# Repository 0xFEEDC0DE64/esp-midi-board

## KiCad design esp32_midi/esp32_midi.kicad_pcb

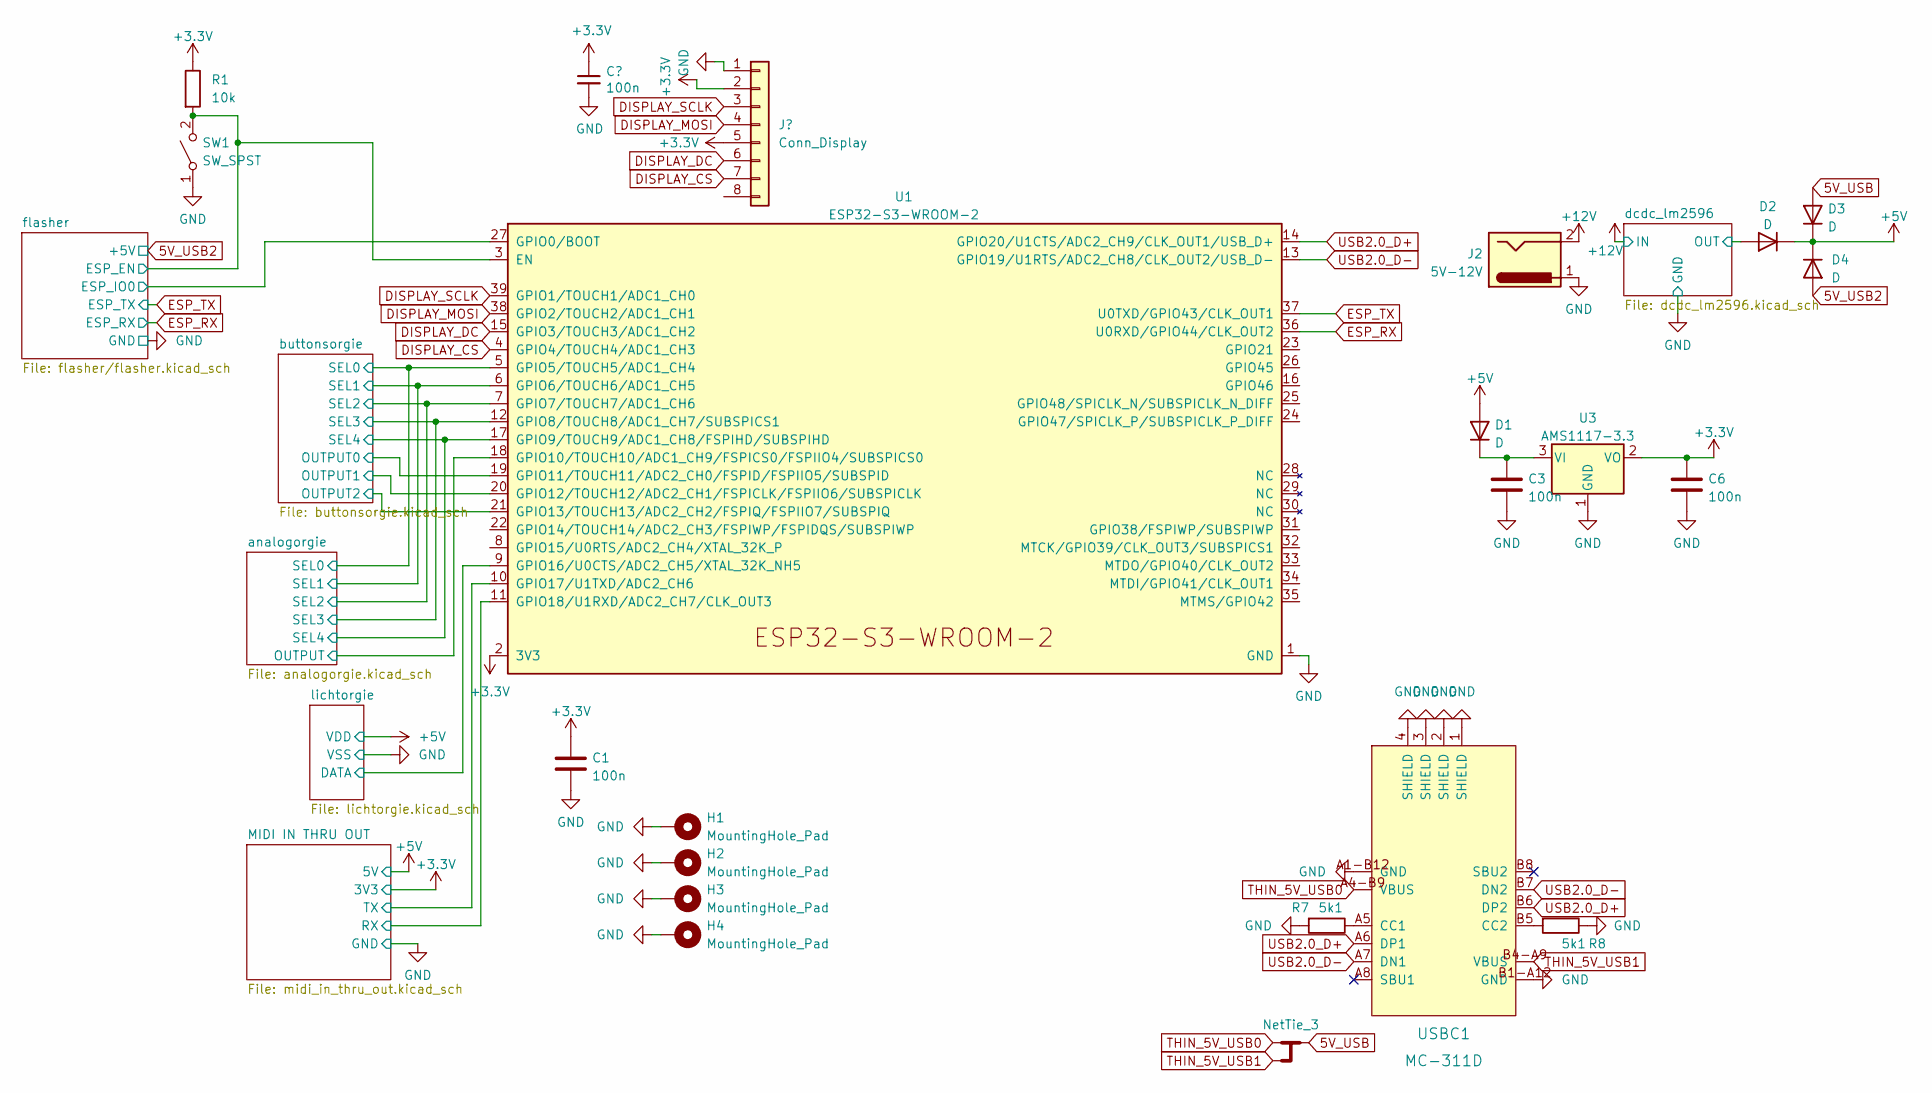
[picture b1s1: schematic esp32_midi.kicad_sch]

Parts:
C1, C3, C6: 100n; C_1206_3216Metric
C2: 100n; C_1206_3216Metric; LCSC Part # C1525
D1, D2, D3, D4: D; D_SOD-123
H1, H2, H3, H4: MountingHole_Pad; MountingHole_4mm_Pad_Via
J1: Conn_Display; PinHeader_1x08_P2.54mm_Vertical
J2: 5V-12V; BarrelJack_Wuerth_6941xx301002
NT102: NetTie_3; NetTie-3_SMD_Pad0.5mm
R1: 10k; R_1206_3216Metric
R7, R8: 5k1; R_1206_3216Metric; LCSC Part # C25905
SW1: SW_SPST; SW_PUSH_6mm_H13mm
U1: ESP32-S3-WROOM-2
U3: AMS1117-3.3; SOT-223-3_TabPin2
USBC1: MC-311D; USB-C-SMD_MC-311D; JLC Part Extended Part

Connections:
5V_USB: D3.2 (A), NT102.2
5V_USB2: D4.2 (A); also elsewhere on the board
+3.3V: C1.1, C2.1, C6.1, J1.2, J1.5, R1.1, U1.2 (3V3), U3.2 (VO); also elsewhere on the board
+5V: D1.2 (A), D2.1 (K), D3.1 (K), D4.1 (K); also elsewhere on the board
+12V: J2.2; also elsewhere on the board
/MIDI IN THRU OUT/RX: U1.11 (GPIO18/U1RXD/ADC2_CH7/CLK_OUT3); also elsewhere on the board
/MIDI IN THRU OUT/TX: U1.10 (GPIO17/U1TXD/ADC2_CH6); also elsewhere on the board
/OUTPUT: U1.18 (GPIO10/TOUCH10/ADC1_CH9/FSPICS0/FSPIIO4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)
/analogorgie/SEL0: U1.5 (GPIO5/TOUCH5/ADC1_CH4); also elsewhere on the board
/analogorgie/SEL1: U1.6 (GPIO6/TOUCH6/ADC1_CH5); also elsewhere on the board
/analogorgie/SEL2: U1.7 (GPIO7/TOUCH7/ADC1_CH6); also elsewhere on the board
/analogorgie/SEL3: U1.12 (GPIO8/TOUCH8/ADC1_CH7/SUBSPICS1); also elsewhere on the board
/analogorgie/SEL4: U1.17 (GPIO9/TOUCH9/ADC1_CH8/FSPIHD/SUBSPIHD); also elsewhere on the board
/buttonsorgie/OUTPUT0: U1.19 (GPIO11/TOUCH11/ADC2_CH0/FSPID/FSPIIO5/S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); also elsewhere on the board
/buttonsorgie/OUTPUT1: U1.20 (GPIO12/TOUCH12/ADC2_CH1/FSPICLK/FSPIIO6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); also elsewhere on the board
/buttonsorgie/OUTPUT2: U1.21 (GPIO13/TOUCH13/ADC2_CH2/FSPIQ/FSPIIO7/S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); also elsewhere on the board
/flasher/ESP_EN: R1.2, SW1.2 (B), U1.3 (EN); also elsewhere on the board
/flasher/ESP_IO0: U1.27 (GPIO0/BOOT); also elsewhere on the board
/lichtorgie/DATA: U1.9 (GPIO16/U0CTS/ADC2_CH5/XTAL_32K_NH5); also elsewhere on the board
DICK1: D2.2 (A); also elsewhere on the board
DISPLAY_CS: J1.7, U1.4 (GPIO4/TOUCH4/ADC1_CH3)
DISPLAY_DC: J1.6, U1.15 (GPIO3/TOUCH3/ADC1_CH2)
DISPLAY_MOSI: J1.4, U1.38 (GPIO2/TOUCH2/ADC1_CH1)
DISPLAY_SCLK: J1.3, U1.39 (GPIO1/TOUCH1/ADC1_CH0)
ESP_RX: U1.36 (U0RXD/GPIO44/CLK_OUT2); also elsewhere on the board
ESP_TX: U1.37 (U0TXD/GPIO43/CLK_OUT1); also elsewhere on the board
GND: C1.2, C2.2, C3.2, C6.2, H1.1, H2.1, H3.1, H4.1, J1.1, J2.1, R7.2, R8.1, SW1.1 (A), U1.1 (GND), U1.40 (GND), U1.41 (GND), U3.1 (GND), USBC1.1 (SHIELD), USBC1.2 (SHIELD), USBC1.3 (SHIELD), USBC1.4 (SHIELD), USBC1.A1-B12 (GND), USBC1.B1-A12 (GND); also elsewhere on the board
unnamed: C3.1, D1.1 (K), U3.3 (VI)
unnamed 400: R7.1; also elsewhere on the board
unnamed 401: R8.2; also elsewhere on the board
THIN_5V_USB0: NT102.1, USBC1.A4-B9 (VBUS); also elsewhere on the board
THIN_5V_USB1: NT102.3, USBC1.B4-A9 (VBUS); also elsewhere on the board
USB2.0_D+: U1.14 (GPIO20/U1CTS/ADC2_CH9/CLK_OUT1/USB_D+), USBC1.A6 (DP1), USBC1.B6 (DP2); also elsewhere on the board
USB2.0_D-: U1.13 (GPIO19/U1RTS/ADC2_CH8/CLK_OUT2/USB_D-), USBC1.A7 (DN1), USBC1.B7 (DN2); also elsewhere on the board

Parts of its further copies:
R51, R52: 5k1; R_1206_3216Metric; LCSC Part # C25905

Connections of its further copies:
GND: R51.2, R52.1; also elsewhere on the board
unnamed 402: R51.1; also elsewhere on the board
unnamed 403: R52.2; also elsewhere on the board

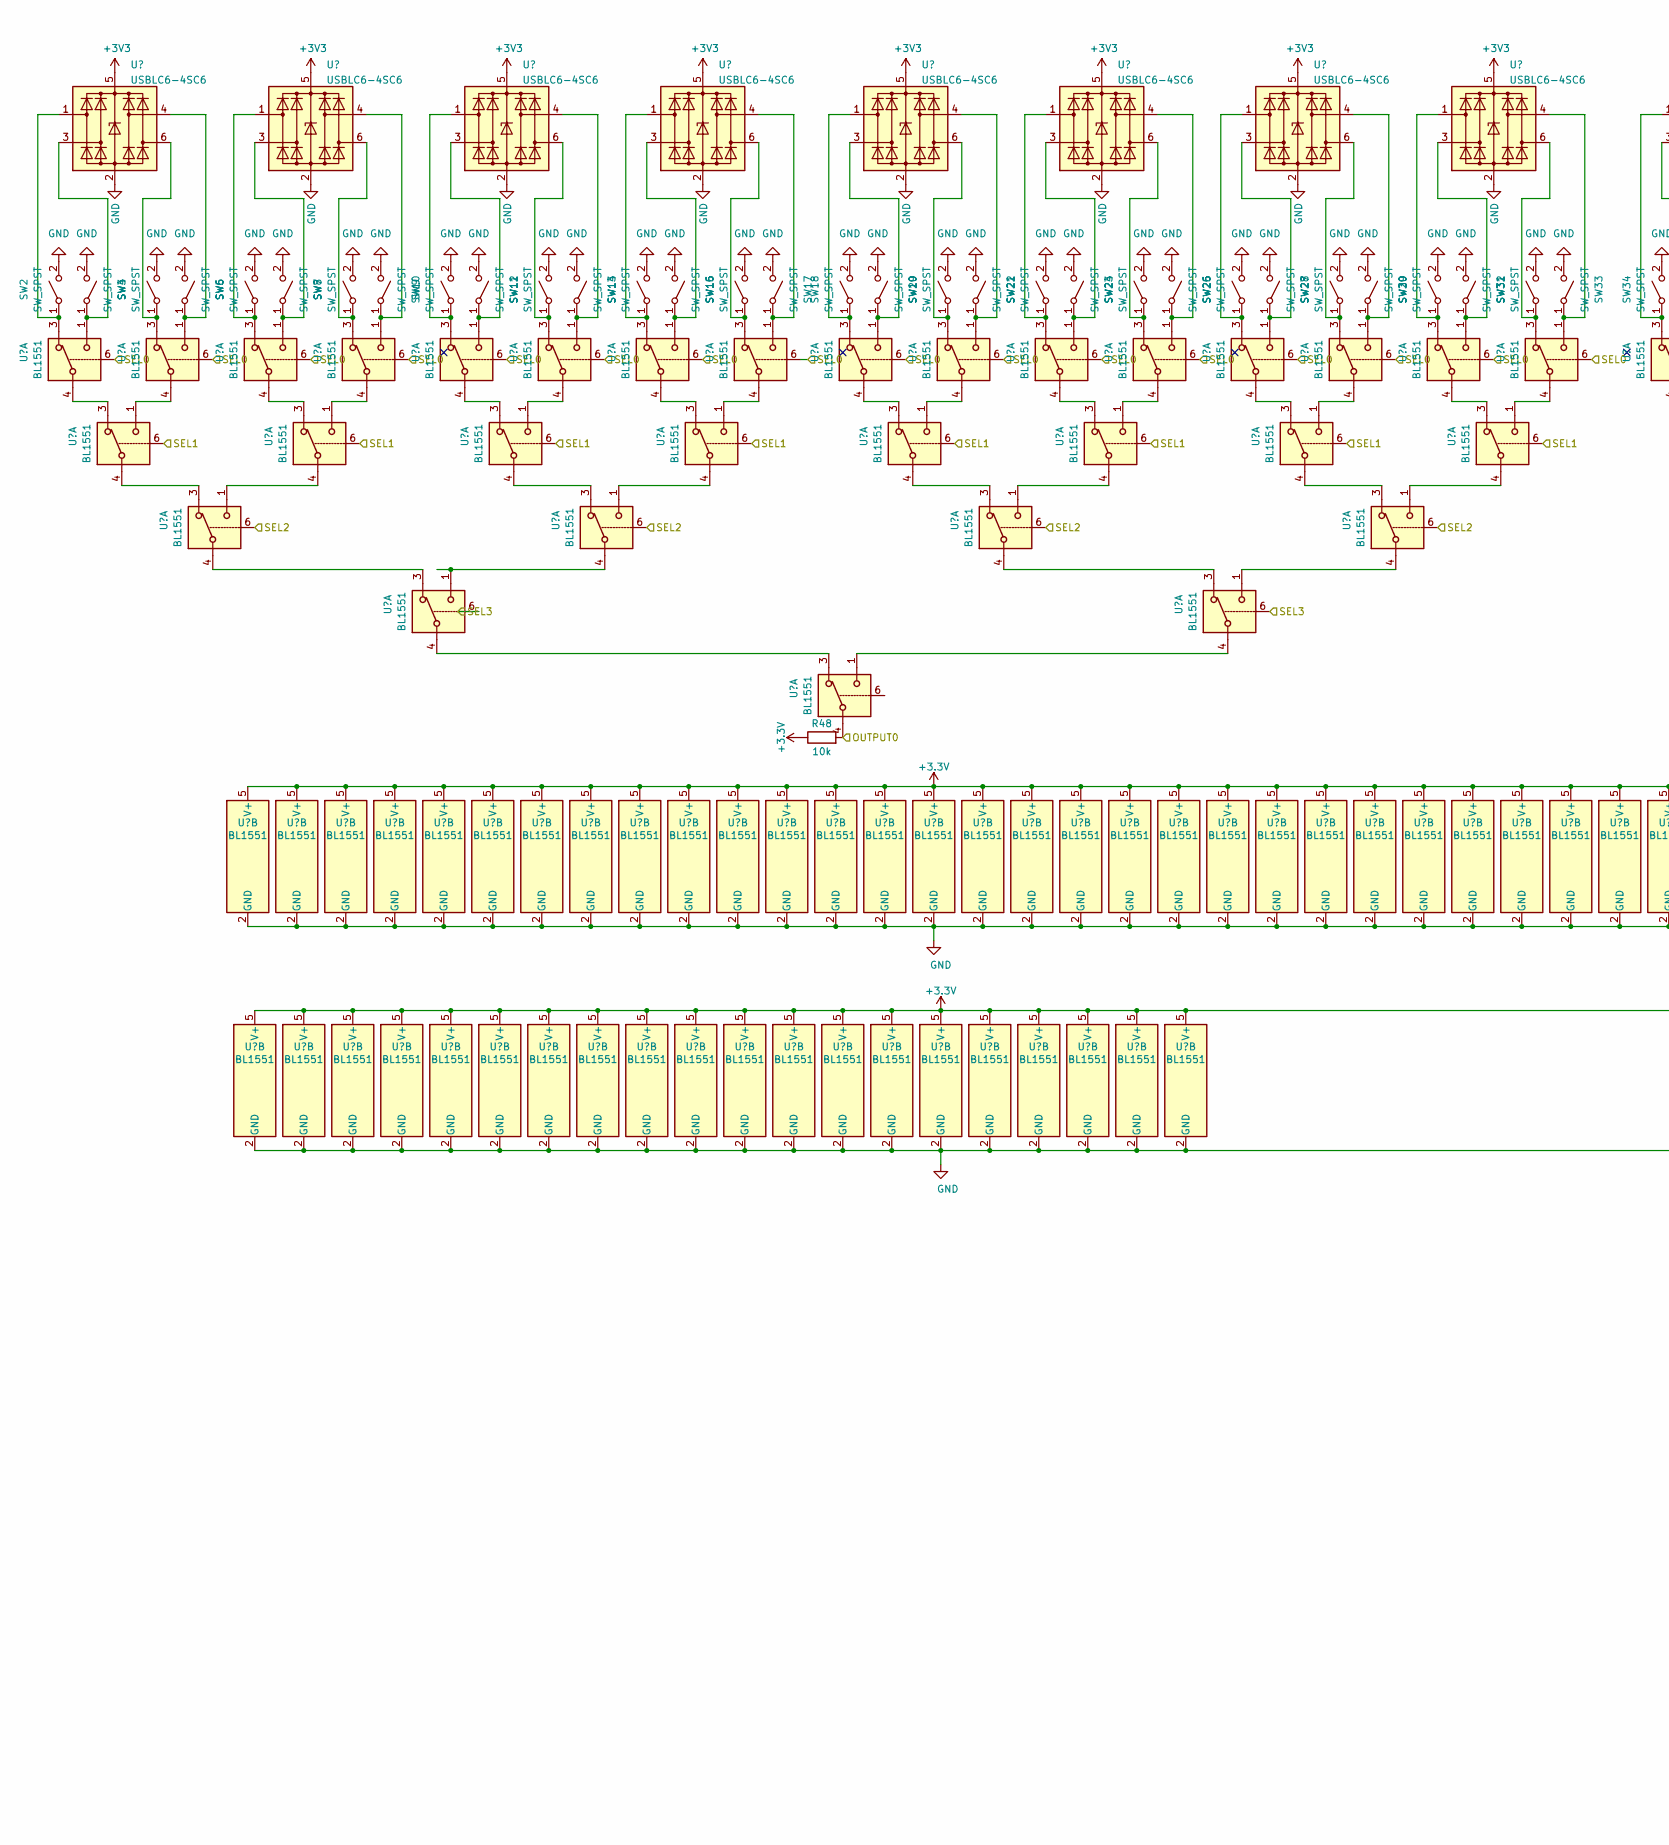
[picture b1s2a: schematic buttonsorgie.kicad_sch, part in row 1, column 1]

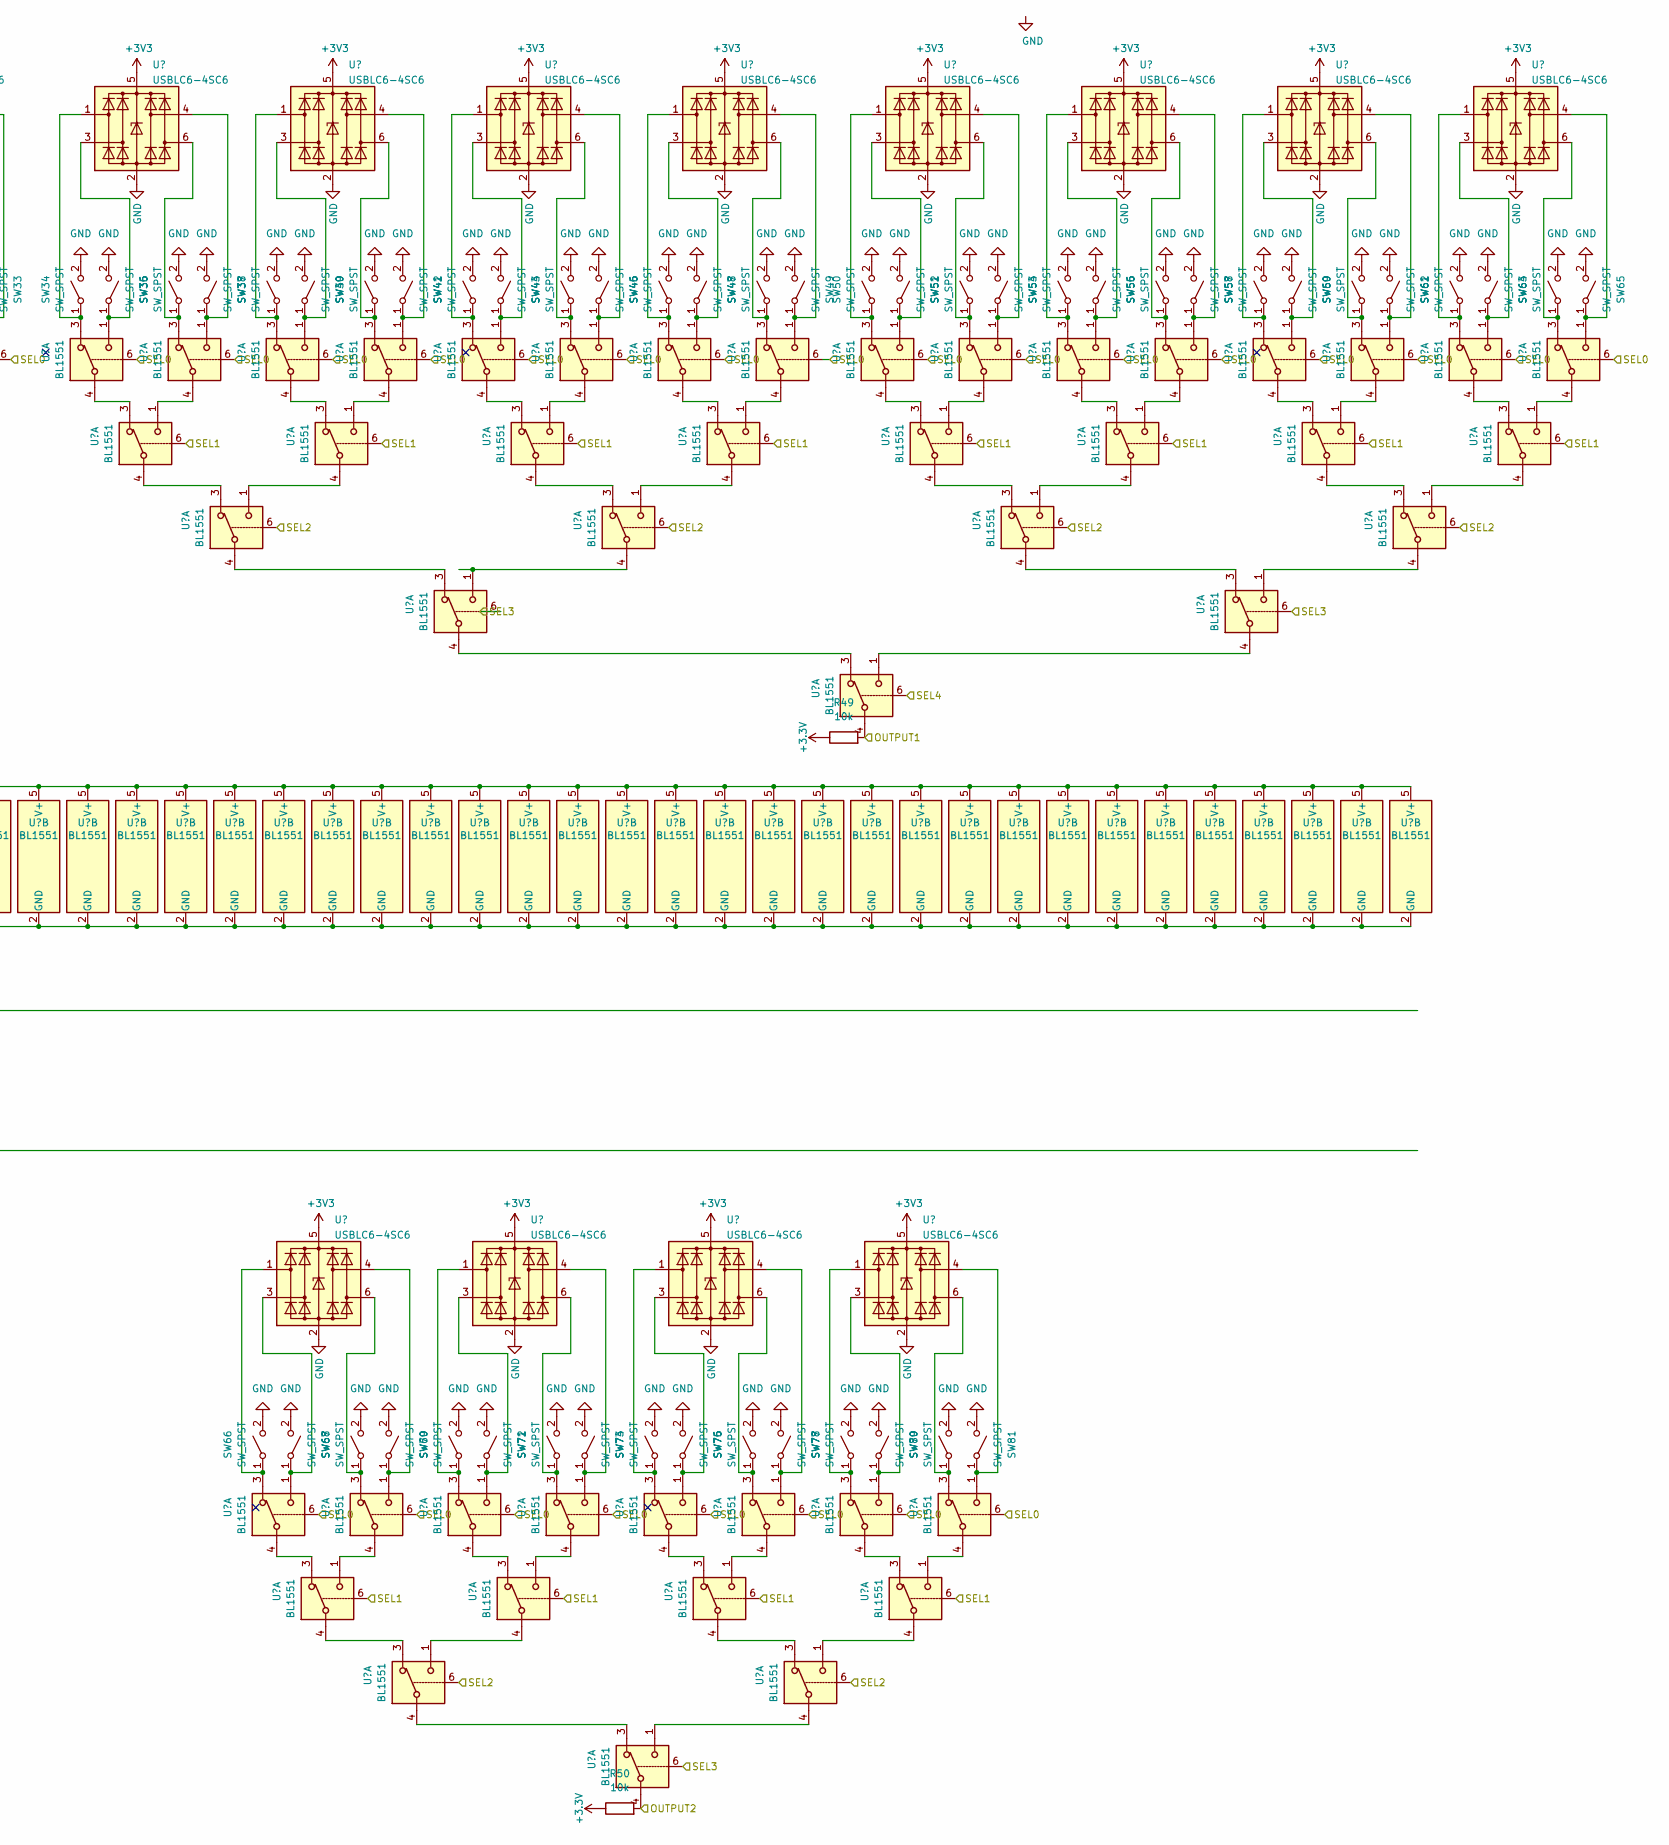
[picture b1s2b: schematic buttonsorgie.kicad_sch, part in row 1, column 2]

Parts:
R48, R49, R50: 10k; R_1206_3216Metric
SW2, SW3, SW4, SW5, SW6, SW7, SW8, SW9, SW10, SW11, SW12, SW13, SW14, SW15, SW16, SW17, SW18, SW19, SW20, SW21, SW22, SW23, SW24, SW25, SW26, SW27, SW28, SW29, SW30, SW31, SW32, SW33, SW34, SW35, SW36, SW37, SW38, SW39, SW40, SW41, SW42, SW43, SW44, SW45, SW46, SW47, SW48, SW49, SW50, SW51, SW52, SW53, SW54, SW55, SW56, SW57, SW58, SW59, SW60, SW61, SW62, SW63, SW64, SW65, SW66, SW67, SW68, SW69, SW70, SW71, SW72, SW73: SW_SPST; scheißbutton
SW74, SW75, SW76, SW77: SW_SPST; bobbybutton
SW78, SW79, SW80, SW81: SW_SPST; PinSocket_1x02_P2.54mm_Vertical
U36, U37, U39, U40, U41, U42, U44, U45, U46, U47, U49, U50, U51, U52, U54, U55, U56, U57, U59, U60, U61, U62, U64, U65, U66, U67, U69, U70, U71, U72, U74, U75, U76, U78, U79, U80, U81, U83, U84, U85, U86, U88, U89, U90, U91, U93, U94, U95, U96, U98, U99, U100, U101, U103, U104, U105, U106, U108, U109, U110, U111, U113, U114, U115, U116, U118, U119, U120, U121, U123, U124, U125, U126, U128, U129, U130, U131, U133: BL1551; SOT-363_SC-70-6
U38, U43, U48, U53, U58, U63, U68, U73, U77, U82, U87, U92, U97, U102, U107, U112, U117, U122, U127, U132: USBLC6-4SC6; SOT-23-6; LCSC Part # C558419

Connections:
+3.3V: R48.1, R49.1, R50.1, U36.5 (V+), U37.5 (V+), U39.5 (V+), U40.5 (V+), U41.5 (V+), U42.5 (V+), U44.5 (V+), U45.5 (V+), U46.5 (V+), U47.5 (V+), U49.5 (V+), U50.5 (V+), U51.5 (V+), U52.5 (V+), U54.5 (V+), U55.5 (V+), U56.5 (V+), U57.5 (V+), U59.5 (V+), U60.5 (V+), U61.5 (V+), U62.5 (V+), U64.5 (V+), U65.5 (V+), U66.5 (V+), U67.5 (V+), U69.5 (V+), U70.5 (V+), U71.5 (V+), U72.5 (V+), U74.5 (V+), U75.5 (V+), U76.5 (V+), U78.5 (V+), U79.5 (V+), U80.5 (V+), U81.5 (V+), U83.5 (V+), U84.5 (V+), U85.5 (V+), U86.5 (V+), U88.5 (V+), U89.5 (V+), U90.5 (V+), U91.5 (V+), U93.5 (V+), U94.5 (V+), U95.5 (V+), U96.5 (V+), U98.5 (V+), U99.5 (V+), U100.5 (V+), U101.5 (V+), U103.5 (V+), U104.5 (V+), U105.5 (V+), U106.5 (V+), U109.5 (V+), U110.5 (V+), U111.5 (V+), U113.5 (V+), U114.5 (V+), U115.5 (V+), U116.5 (V+), U118.5 (V+), U119.5 (V+), U120.5 (V+), U121.5 (V+), U123.5 (V+), U124.5 (V+), U125.5 (V+), U126.5 (V+), U128.5 (V+), U129.5 (V+), U130.5 (V+), U131.5 (V+), U133.5 (V+); also elsewhere on the board
+3V3: U38.5 (VBUS), U43.5 (VBUS), U48.5 (VBUS), U53.5 (VBUS), U58.5 (VBUS), U63.5 (VBUS), U68.5 (VBUS), U73.5 (VBUS), U77.5 (VBUS), U82.5 (VBUS), U87.5 (VBUS), U92.5 (VBUS), U97.5 (VBUS), U102.5 (VBUS), U107.5 (VBUS), U112.5 (VBUS), U117.5 (VBUS), U122.5 (VBUS), U127.5 (VBUS), U132.5 (VBUS); also elsewhere on the board
/analogorgie/SEL0: U36.6, U39.6, U41.6, U44.6, U46.6, U49.6, U51.6, U54.6, U56.6, U59.6, U61.6, U64.6, U66.6, U69.6, U71.6, U74.6, U75.6, U78.6, U80.6, U83.6, U85.6, U88.6, U90.6, U93.6, U95.6, U98.6, U100.6, U103.6, U105.6, U108.6, U110.6, U113.6, U115.6, U118.6, U120.6, U123.6, U125.6, U128.6, U130.6, U133.6; also elsewhere on the board
/analogorgie/SEL1: U37.6, U42.6, U47.6, U52.6, U57.6, U62.6, U67.6, U72.6, U76.6, U81.6, U86.6, U91.6, U96.6, U101.6, U106.6, U111.6, U116.6, U121.6, U126.6, U131.6; also elsewhere on the board
/analogorgie/SEL2: U40.6, U50.6, U60.6, U70.6, U79.6, U89.6, U99.6, U109.6, U119.6, U129.6; also elsewhere on the board
/analogorgie/SEL3: U45.6, U65.6, U84.6, U104.6, U124.6; also elsewhere on the board
/analogorgie/SEL4: U94.6; also elsewhere on the board
/buttonsorgie/OUTPUT0: R48.2, U55.4; also elsewhere on the board
/buttonsorgie/OUTPUT1: R49.2, U94.4; also elsewhere on the board
/buttonsorgie/OUTPUT2: R50.2, U124.4; also elsewhere on the board
GND: SW2.2 (B), SW3.2 (B), SW4.2 (B), SW5.2 (B), SW6.2 (B), SW7.2 (B), SW8.2 (B), SW9.2 (B), SW10.2 (B), SW11.2 (B), SW12.2 (B), SW13.2 (B), SW14.2 (B), SW15.2 (B), SW16.2 (B), SW17.2 (B), SW18.2 (B), SW19.2 (B), SW20.2 (B), SW21.2 (B), SW22.2 (B), SW23.2 (B), SW24.2 (B), SW25.2 (B), SW26.2 (B), SW27.2 (B), SW28.2 (B), SW29.2 (B), SW30.2 (B), SW31.2 (B), SW32.2 (B), SW33.2 (B), SW34.2 (B), SW35.2 (B), SW36.2 (B), SW37.2 (B), SW38.2 (B), SW39.2 (B), SW40.2 (B), SW41.2 (B), SW42.2 (B), SW43.2 (B), SW44.2 (B), SW45.2 (B), SW46.2 (B), SW47.2 (B), SW48.2 (B), SW49.2 (B), SW50.2 (B), SW51.2 (B), SW52.2 (B), SW53.2 (B), SW54.2 (B), SW55.2 (B), SW56.2 (B), SW57.2 (B), SW58.2 (B), SW59.2 (B), SW60.2 (B), SW61.2 (B), SW62.2 (B), SW63.2 (B), SW64.2 (B), SW65.2 (B), SW66.2 (B), SW67.2 (B), SW68.2 (B), SW69.2 (B), SW70.2 (B), SW71.2 (B), SW72.2 (B), SW73.2 (B), SW74.2 (B), SW75.2 (B), SW76.2 (B), SW77.2 (B), SW78.2 (B), SW79.2 (B), SW80.2 (B), SW81.2 (B), U36.2 (GND), U37.2 (GND), U38.2 (GND), U39.2 (GND), U40.2 (GND), U41.2 (GND), U42.2 (GND), U43.2 (GND), U44.2 (GND), U45.2 (GND), U46.2 (GND), U47.2 (GND), U48.2 (GND), U49.2 (GND), U50.2 (GND), U51.2 (GND), U52.2 (GND), U53.2 (GND), U54.2 (GND), U55.2 (GND), U56.2 (GND), U57.2 (GND), U58.2 (GND), U59.2 (GND), U60.2 (GND), U61.2 (GND), U62.2 (GND), U63.2 (GND), U64.2 (GND), U65.2 (GND), U66.2 (GND), U67.2 (GND), U68.2 (GND), U69.2 (GND), U70.2 (GND), U71.2 (GND), U72.2 (GND), U73.2 (GND), U74.2 (GND), U75.2 (GND), U76.2 (GND), U77.2 (GND), U78.2 (GND), U79.2 (GND), U80.2 (GND), U81.2 (GND), U82.2 (GND), U83.2 (GND), U84.2 (GND), U85.2 (GND), U86.2 (GND), U87.2 (GND), U88.2 (GND), U89.2 (GND), U90.2 (GND), U91.2 (GND), U92.2 (GND), U93.2 (GND), U94.2 (GND), U95.2 (GND), U96.2 (GND), U97.2 (GND), U98.2 (GND), U99.2 (GND), U100.2 (GND), U101.2 (GND), U102.2 (GND), U103.2 (GND), U104.2 (GND), U105.2 (GND), U106.2 (GND), U107.2 (GND), U109.2 (GND), U110.2 (GND), U111.2 (GND), U112.2 (GND), U113.2 (GND), U114.2 (GND), U115.2 (GND), U116.2 (GND), U117.2 (GND), U118.2 (GND), U119.2 (GND), U120.2 (GND), U121.2 (GND), U122.2 (GND), U123.2 (GND), U124.2 (GND), U125.2 (GND), U126.2 (GND), U127.2 (GND), U128.2 (GND), U129.2 (GND), U130.2 (GND), U131.2 (GND), U132.2 (GND), U133.2 (GND); also elsewhere on the board
unnamed: SW2.1 (A), U36.3, U38.1 (I/O1)
unnamed: SW3.1 (A), U36.1, U38.3 (I/O2)
unnamed: SW4.1 (A), U38.6 (I/O4), U39.3
unnamed: SW5.1 (A), U38.4 (I/O3), U39.1
unnamed: SW6.1 (A), U41.3, U43.1 (I/O1)
unnamed: SW7.1 (A), U41.1, U43.3 (I/O2)
unnamed: SW8.1 (A), U43.6 (I/O4), U44.3
unnamed: SW9.1 (A), U43.4 (I/O3), U44.1
unnamed: SW10.1 (A), U46.3, U48.1 (I/O1)
unnamed: SW11.1 (A), U46.1, U48.3 (I/O2)
unnamed: SW12.1 (A), U48.6 (I/O4), U49.3
unnamed: SW13.1 (A), U48.4 (I/O3), U49.1
unnamed: SW14.1 (A), U51.3, U53.1 (I/O1)
unnamed: SW15.1 (A), U51.1, U53.3 (I/O2)
unnamed: SW16.1 (A), U53.6 (I/O4), U54.3
unnamed: SW17.1 (A), U53.4 (I/O3), U54.1
unnamed: SW18.1 (A), U56.3, U58.1 (I/O1)
unnamed: SW19.1 (A), U56.1, U58.3 (I/O2)
unnamed: SW20.1 (A), U58.6 (I/O4), U59.3
unnamed: SW21.1 (A), U58.4 (I/O3), U59.1
unnamed: SW22.1 (A), U61.3, U63.1 (I/O1)
unnamed: SW23.1 (A), U61.1, U63.3 (I/O2)
unnamed: SW24.1 (A), U63.6 (I/O4), U64.3
unnamed: SW25.1 (A), U63.4 (I/O3), U64.1
unnamed: SW26.1 (A), U66.3, U68.1 (I/O1)
unnamed: SW27.1 (A), U66.1, U68.3 (I/O2)
unnamed: SW28.1 (A), U68.6 (I/O4), U69.3
unnamed: SW29.1 (A), U68.4 (I/O3), U69.1
unnamed: SW30.1 (A), U71.3, U73.1 (I/O1)
unnamed: SW31.1 (A), U71.1, U73.3 (I/O2)
unnamed: SW32.1 (A), U73.6 (I/O4), U74.3
unnamed: SW33.1 (A), U73.4 (I/O3), U74.1
unnamed: SW34.1 (A), U75.3, U77.1 (I/O1)
unnamed: SW35.1 (A), U75.1, U77.3 (I/O2)
unnamed: SW36.1 (A), U77.6 (I/O4), U78.3
unnamed: SW37.1 (A), U77.4 (I/O3), U78.1
unnamed: SW38.1 (A), U80.3, U82.1 (I/O1)
unnamed: SW39.1 (A), U80.1, U82.3 (I/O2)
unnamed: SW40.1 (A), U82.6 (I/O4), U83.3
unnamed: SW41.1 (A), U82.4 (I/O3), U83.1
unnamed: SW42.1 (A), U85.3, U87.1 (I/O1)
unnamed: SW43.1 (A), U85.1, U87.3 (I/O2)
unnamed: SW44.1 (A), U87.6 (I/O4), U88.3
unnamed: SW45.1 (A), U87.4 (I/O3), U88.1
unnamed: SW46.1 (A), U90.3, U92.1 (I/O1)
unnamed: SW47.1 (A), U90.1, U92.3 (I/O2)
unnamed: SW48.1 (A), U92.6 (I/O4), U93.3
unnamed: SW49.1 (A), U92.4 (I/O3), U93.1
unnamed: SW50.1 (A), U95.3, U97.1 (I/O1)
unnamed: SW51.1 (A), U95.1, U97.3 (I/O2)
unnamed: SW52.1 (A), U97.6 (I/O4), U98.3
unnamed: SW53.1 (A), U97.4 (I/O3), U98.1
unnamed: SW54.1 (A), U100.3, U102.1 (I/O1)
unnamed: SW55.1 (A), U100.1, U102.3 (I/O2)
unnamed: SW56.1 (A), U102.6 (I/O4), U103.3
unnamed: SW57.1 (A), U102.4 (I/O3), U103.1
unnamed: SW58.1 (A), U105.3, U107.1 (I/O1)
unnamed: SW59.1 (A), U105.1, U107.3 (I/O2)
unnamed: SW60.1 (A), U107.6 (I/O4), U108.3
unnamed: SW61.1 (A), U107.4 (I/O3), U108.1
unnamed: SW62.1 (A), U110.3, U112.1 (I/O1)
unnamed: SW63.1 (A), U110.1, U112.3 (I/O2)
unnamed: SW64.1 (A), U112.6 (I/O4), U113.3
unnamed: SW65.1 (A), U112.4 (I/O3), U113.1
unnamed: SW66.1 (A), U115.3, U117.1 (I/O1)
unnamed: SW67.1 (A), U115.1, U117.3 (I/O2)
unnamed: SW68.1 (A), U117.6 (I/O4), U118.3
unnamed: SW69.1 (A), U117.4 (I/O3), U118.1
unnamed: SW70.1 (A), U120.3, U122.1 (I/O1)
unnamed: SW71.1 (A), U120.1, U122.3 (I/O2)
unnamed: SW72.1 (A), U122.6 (I/O4), U123.3
unnamed: SW73.1 (A), U122.4 (I/O3), U123.1
unnamed: SW74.1 (A), U125.3, U127.1 (I/O1)
unnamed: SW75.1 (A), U125.1, U127.3 (I/O2)
unnamed: SW76.1 (A), U127.6 (I/O4), U128.3
unnamed: SW77.1 (A), U127.4 (I/O3), U128.1
unnamed: SW78.1 (A), U130.3, U132.1 (I/O1)
unnamed: SW79.1 (A), U130.1, U132.3 (I/O2)
unnamed: SW80.1 (A), U132.6 (I/O4), U133.3
unnamed: SW81.1 (A), U132.4 (I/O3), U133.1
unnamed: U36.4, U37.3
unnamed: U37.1, U39.4
unnamed: U37.4, U40.3
unnamed: U40.1, U42.4
unnamed: U40.4, U45.3
unnamed: U41.4, U42.3
unnamed: U42.1, U44.4
unnamed: U45.1, U50.4
unnamed: U45.4, U55.3
unnamed: U46.4, U47.3
unnamed: U47.1, U49.4
unnamed: U47.4, U50.3
unnamed: U50.1, U52.4
unnamed: U51.4, U52.3
unnamed: U52.1, U54.4
unnamed: U55.1, U65.4
unnamed: U56.4, U57.3
unnamed: U57.1, U59.4
unnamed: U57.4, U60.3
unnamed: U60.1, U62.4
unnamed: U60.4, U65.3
unnamed: U61.4, U62.3
unnamed: U62.1, U64.4
unnamed: U65.1, U70.4
unnamed: U66.4, U67.3
unnamed: U67.1, U69.4
unnamed: U67.4, U70.3
unnamed: U70.1, U72.4
unnamed: U71.4, U72.3
unnamed: U72.1, U74.4
unnamed: U75.4, U76.3
unnamed: U76.1, U78.4
unnamed: U76.4, U79.3
unnamed: U79.1, U81.4
unnamed: U79.4, U84.3
unnamed: U80.4, U81.3
unnamed: U81.1, U83.4
unnamed: U84.1, U89.4
unnamed: U84.4, U94.3
unnamed: U85.4, U86.3
unnamed: U86.1, U88.4
unnamed: U86.4, U89.3
unnamed: U89.1, U91.4
unnamed: U90.4, U91.3
unnamed: U91.1, U93.4
unnamed: U95.4, U96.3
unnamed: U96.1, U98.4
unnamed: U96.4, U99.3
unnamed: U100.4, U101.3
unnamed: U101.1, U103.4
unnamed: U99.1, U101.4
unnamed: U104.1, U109.4
unnamed: U99.4, U104.3
unnamed: U94.1, U104.4
unnamed: U105.4, U106.3
unnamed: U106.1, U108.4
unnamed: U106.4, U109.3
unnamed: U109.1, U111.4
unnamed: U110.4, U111.3
unnamed: U111.1, U113.4
unnamed: U115.4, U116.3
unnamed: U116.1, U118.4
unnamed: U116.4, U119.3
unnamed: U119.1, U121.4
unnamed: U119.4, U124.3
unnamed: U120.4, U121.3
unnamed: U121.1, U123.4
unnamed: U124.1, U129.4
unnamed: U125.4, U126.3
unnamed: U126.1, U128.4
unnamed: U126.4, U129.3
unnamed: U129.1, U131.4
unnamed: U130.4, U131.3
unnamed: U131.1, U133.4
